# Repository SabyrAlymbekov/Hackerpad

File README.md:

# **Hackerpad (or Catpad)**

## **About**

This is a custom mechanical macropad (Hackerpad), designed entirely from scratch (my first time btw).

## **Inspiration**

I wanted cool looking macropad for Competitive programming, so I made this one. The design is inspired by cyberpunk aesthetics and orpheuspad design. The device features 5 mechanical keys, a rotary encoder for multimedia control, an OLED display, and RGB lighting.

## **Features**

* **5 Mechanical Keys (Cherry MX):** Programmable macros for VS Code and terminal commands.  
* **Rotary Encoder (EC11):** Smooth volume control and scrolling.  
* **OLED Display (0.91"):** Displays active layers, WPM (words per minute), or Bongo Cat animations.  
* **Per-Key RGB:** Light (SK6812 MINI-E).  
* **Sandwich Case Design:** Designed in Fusion 360 for easy 3D printing and glueless assembly.  
* **Silkscreen art** Unique silkscreen art on the PCB.

## **BOM**

| Component | Quantity | Description | Notes |
| :---- | :---- | :---- | :---- |
| Microcontroller | 1 | XIAO RP2040 DIP | Brain of the device |
| Switches | 5 | Cherry MX | Mechanical switches |
| Keycaps | 5 | DSA profile (blank) | Keycaps |
| Diodes | 6 | 1N4148 (through hole) | For anti-ghosting |
| Encoder | 1 | EC11 rotary encoder | With push button |
| Display | 1 | 0.91" OLED I2C (128x32) | Pinout: GND-VCC-SCL-SDA |
| Pin Header | 1 | 1x4 pin header (2.54mm) | For connecting the display |
| LEDs | 2 | SK6812 MINI-E | Addressable RGB LEDs |
| Screws | 4 | M3 x 10mm | Case screws |
| Inserts | 4 | M3 heatset inserts | Threaded inserts |

## **PCB**

The PCB was designed in **KiCad**.

* **Size:** 97.7mm x 57.15mm.  
* **Layers:** 2 Layers (Top & Bottom).  

### **Layout Screenshots**

| Schematic | Routing | 3D View |
| :---- | :---- | :---- |
|  |  |  |

## **Case Design**

The case was designed in **Autodesk Fusion 360**. It uses a "Sandwich" construction consisting of two parts:

1. **Bottom Case**  
2. **Top Case**

Printable files (.step) can be found in the /cad folder.

## **📂 Repository Structure**

├── cad/                 \# 3D printing files (STL, STEP, F3D)  
├── pcb/                 \# KiCad project (schematic, board, gerbers)  
├── firmware/            \# Source code (main.py)  
├── assets/              \# Renders and photos for README  
└── README.md            \# This file

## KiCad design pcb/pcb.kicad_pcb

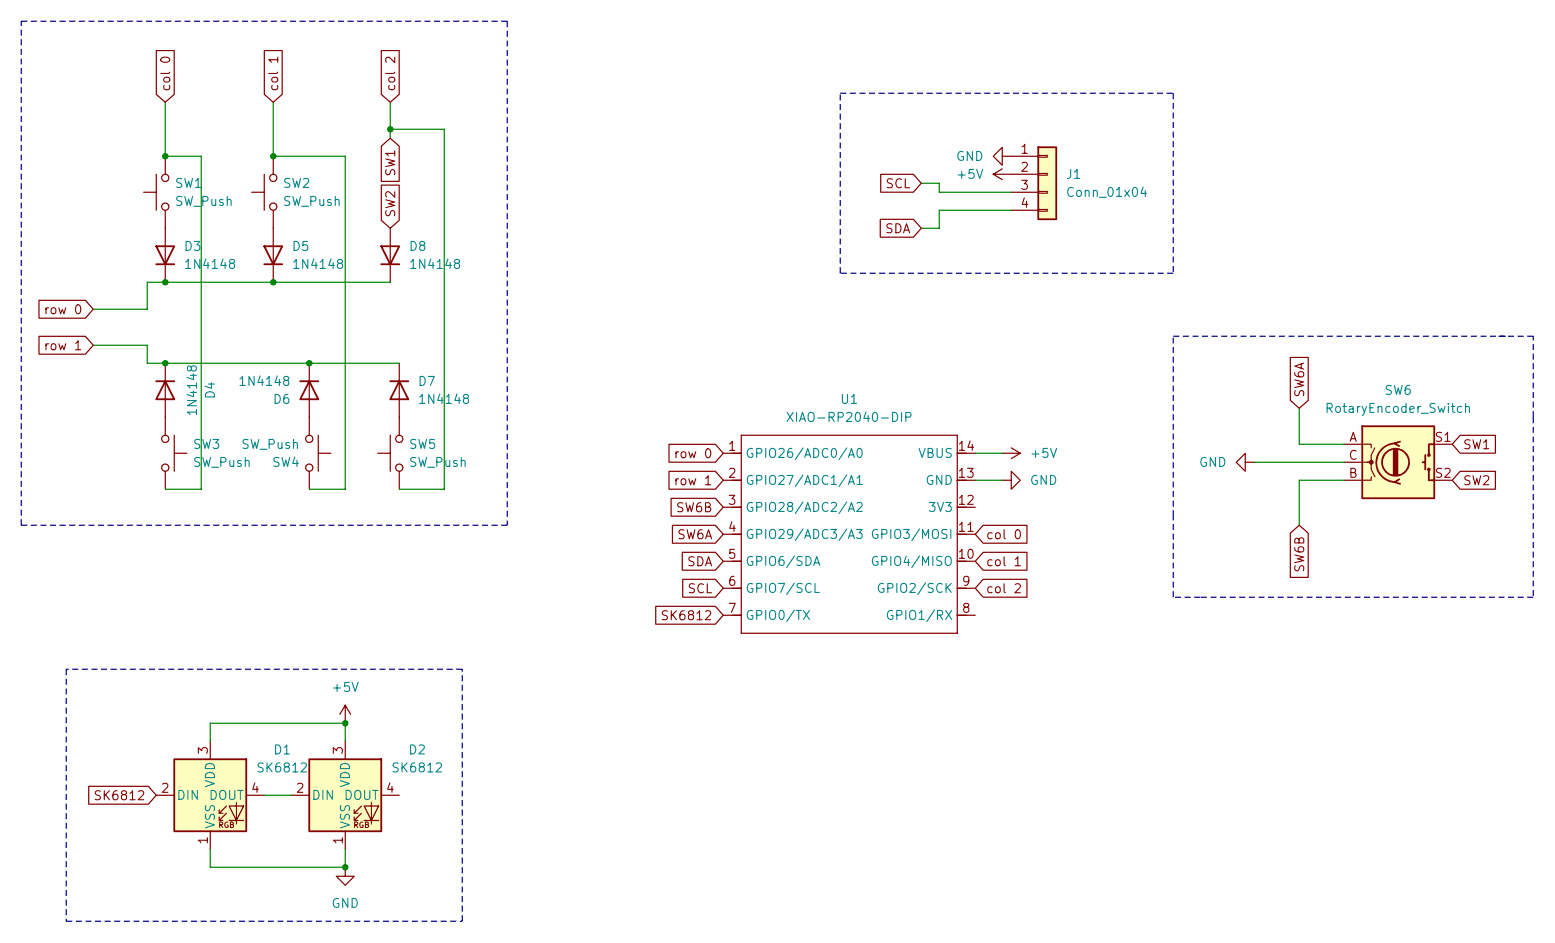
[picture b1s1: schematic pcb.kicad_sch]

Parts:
D1, D2: SK6812; LED_SK6812_PLCC4_5.0x5.0mm_P3.2mm
D3, D4, D5, D6, D7, D8: 1N4148; D_DO-35_SOD27_P7.62mm_Horizontal
J1: Conn_01x04; PinHeader_1x04_P2.54mm_Vertical
SW1, SW2, SW3, SW4, SW5: SW_Push; SW_Cherry_MX_1.00u_PCB
SW6: RotaryEncoder_Switch; RotaryEncoder_Alps_EC11E-Switch_Vertical_H20mm
U1: XIAO-RP2040-DIP

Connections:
+5V: D1.3 (VDD), D2.3 (VDD), J1.2, U1.14 (VBUS)
GND: D1.1 (VSS), D2.1 (VSS), J1.1, SW6.C, U1.13 (GND)
unnamed: D1.4 (DOUT), D2.2 (DIN)
unnamed: D3.2 (A), SW1.1
unnamed: D4.2 (A), SW3.1
unnamed: D5.2 (A), SW2.1
unnamed: D6.2 (A), SW4.1
unnamed: D7.2 (A), SW5.2
SCL: J1.3, U1.6 (GPIO7/SCL)
SDA: J1.4, U1.5 (GPIO6/SDA)
SK6812: D1.2 (DIN), U1.7 (GPIO0/TX)
SW1: SW5.1, SW6.S1, U1.9 (GPIO2/SCK)
SW2: D8.2 (A), SW6.S2
SW6A: SW6.A, U1.4 (GPIO29/ADC3/A3)
SW6B: SW6.B, U1.3 (GPIO28/ADC2/A2)
col 0: SW1.2, SW3.2, U1.11 (GPIO3/MOSI)
col 1: SW2.2, SW4.2, U1.10 (GPIO4/MISO)
row 0: D3.1 (K), D5.1 (K), D8.1 (K), U1.1 (GPIO26/ADC0/A0)
row 1: D4.1 (K), D6.1 (K), D7.1 (K), U1.2 (GPIO27/ADC1/A1)

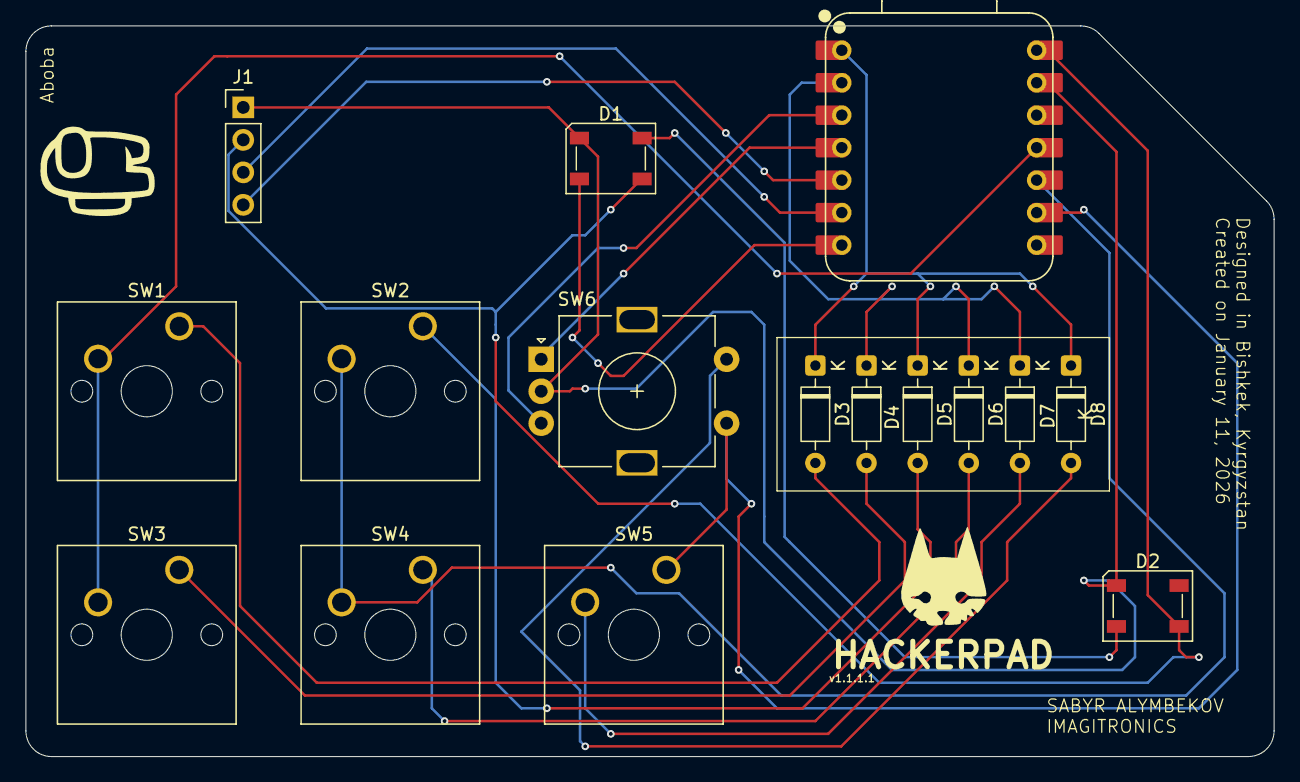
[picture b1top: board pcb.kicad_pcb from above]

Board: 2 copper layers, 97.6 x 57.2 mm, 18 parts (0 on the bottom side), 19 nets.

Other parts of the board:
 : LOGO
 #2: LOGO

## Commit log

2026-01-11 added gerbers.zip
2026-01-12 Add MIT License to the project
2026-01-12 updated readme and added BOM csv and LICENSE
2026-01-13 added design source files and separate files of components
